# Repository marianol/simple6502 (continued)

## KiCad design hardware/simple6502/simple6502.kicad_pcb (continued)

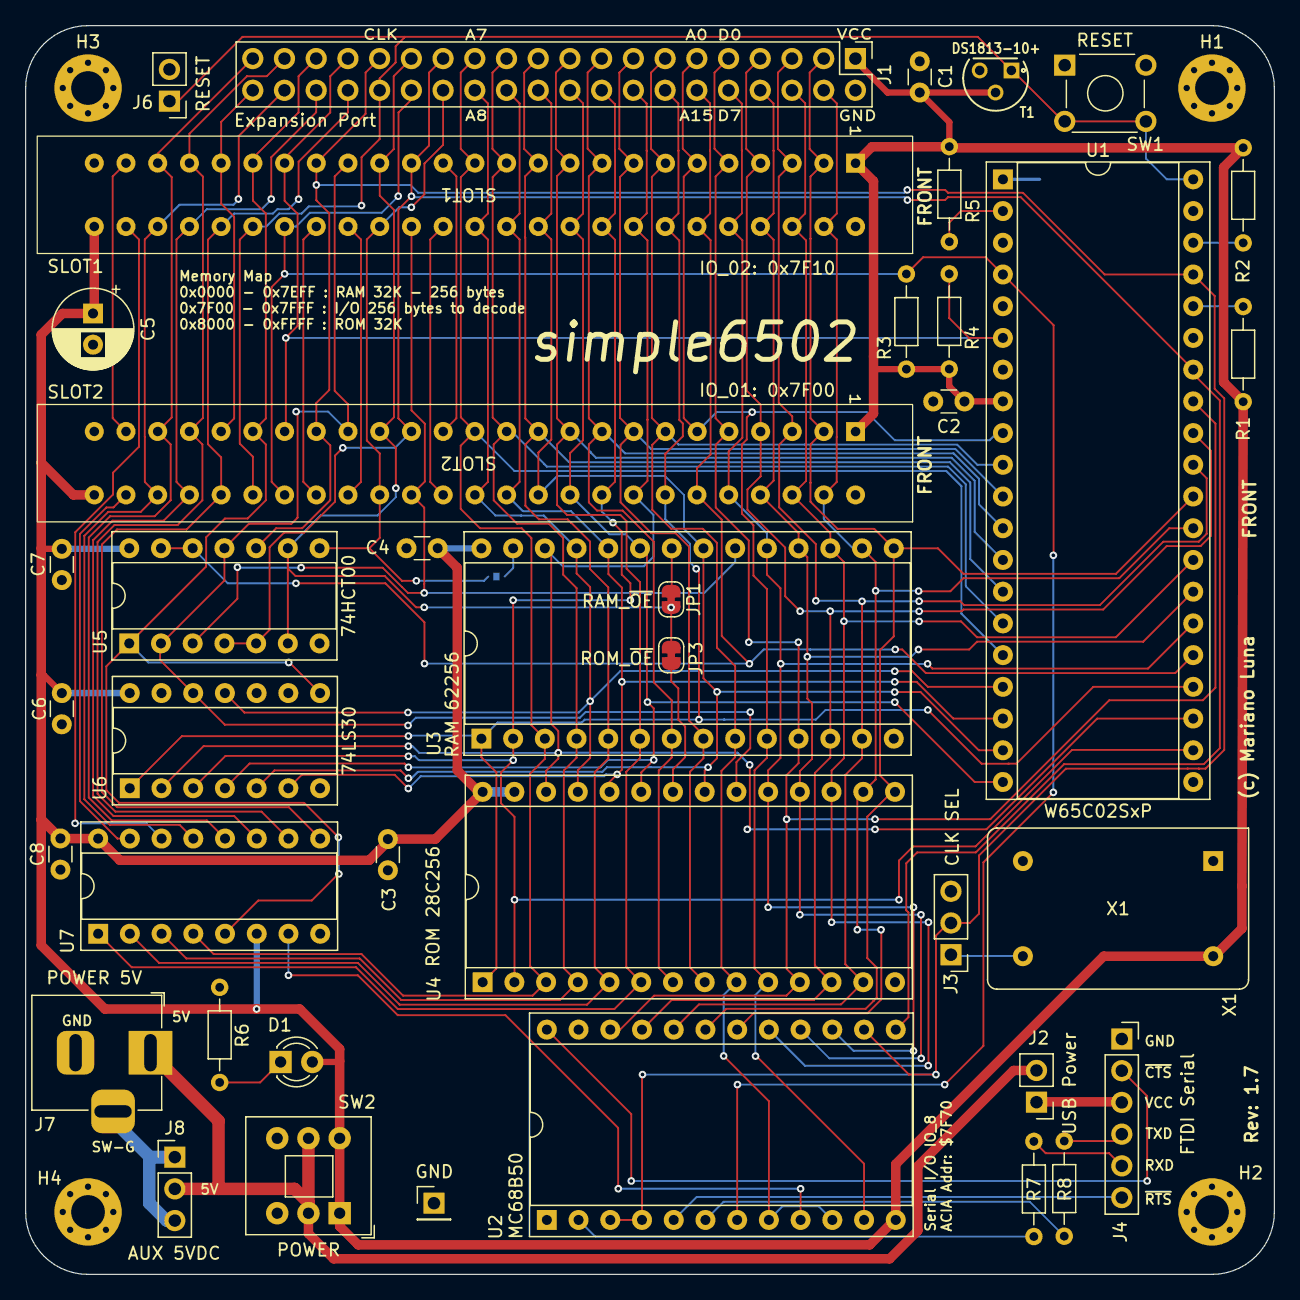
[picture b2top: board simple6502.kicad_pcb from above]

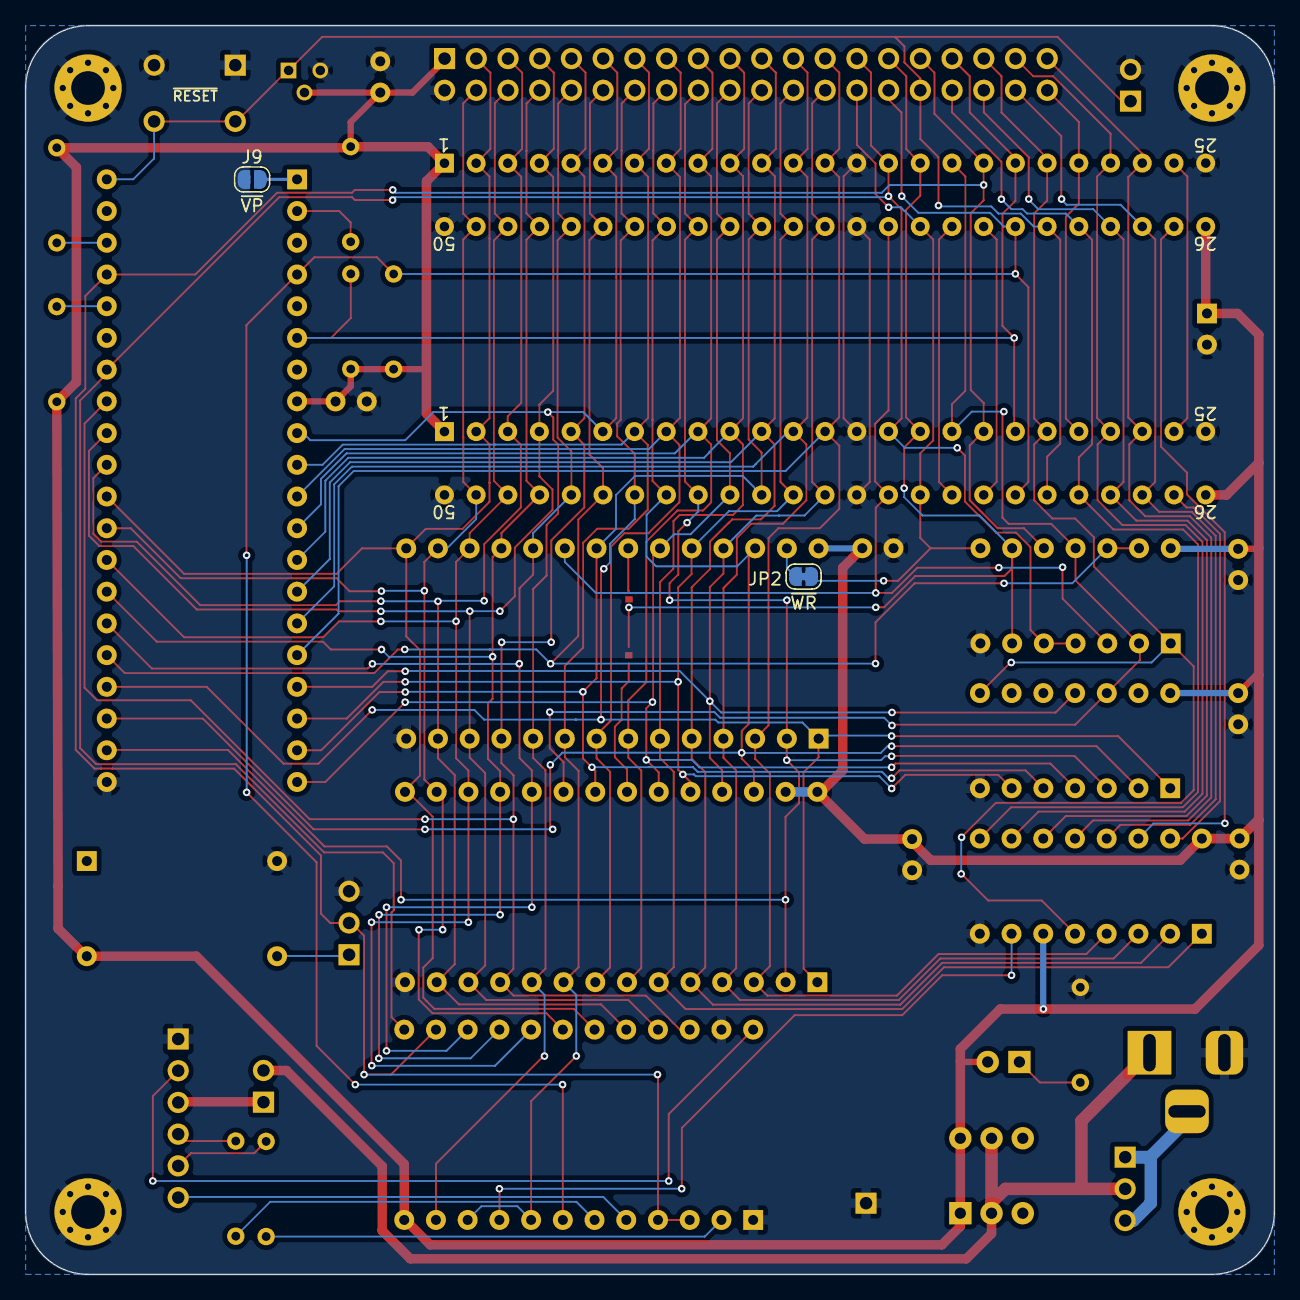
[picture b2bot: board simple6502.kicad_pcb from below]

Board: 2 copper layers, 100.0 x 100.0 mm, 46 parts (2 on the bottom side), 66 nets.

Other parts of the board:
SLOT1: IO_02: 0x7F10; EDAC 395-050-520-201

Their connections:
A0: SLOT1.6; also elsewhere on the board
A1: SLOT1.7; also elsewhere on the board
A2: SLOT1.8; also elsewhere on the board
A3: SLOT1.9; also elsewhere on the board
A4: SLOT1.10; also elsewhere on the board
A5: SLOT1.11; also elsewhere on the board
A6: SLOT1.12; also elsewhere on the board
A7: SLOT1.13; also elsewhere on the board
A8: SLOT1.38; also elsewhere on the board
A9: SLOT1.39; also elsewhere on the board
A10: SLOT1.40; also elsewhere on the board
A11: SLOT1.41; also elsewhere on the board
A12: SLOT1.42; also elsewhere on the board
A13: SLOT1.43; also elsewhere on the board
A14: SLOT1.44; also elsewhere on the board
A15: SLOT1.45; also elsewhere on the board
BUS_21: SLOT1.21; also elsewhere on the board
BUS_24: SLOT1.24; also elsewhere on the board
BUS_33: SLOT1.33; also elsewhere on the board
BUS_34: SLOT1.34; also elsewhere on the board
CLK: SLOT1.18; also elsewhere on the board
D0: SLOT1.5; also elsewhere on the board
D1: SLOT1.4; also elsewhere on the board
D2: SLOT1.3; also elsewhere on the board
D3: SLOT1.2; also elsewhere on the board
D4: SLOT1.49; also elsewhere on the board
D5: SLOT1.48; also elsewhere on the board
D6: SLOT1.47; also elsewhere on the board
D7: SLOT1.46; also elsewhere on the board
GND: SLOT1.14, SLOT1.25, SLOT1.37, SLOT1.50; also elsewhere on the board
R~W: SLOT1.15; also elsewhere on the board
VCC: SLOT1.1, SLOT1.26; also elsewhere on the board
~IO_02: SLOT1.27; also elsewhere on the board
~IO_03: SLOT1.28; also elsewhere on the board
~IO_04: SLOT1.23; also elsewhere on the board
~IO_05: SLOT1.29; also elsewhere on the board
~IO_06: SLOT1.22; also elsewhere on the board
~IO_07: SLOT1.30; also elsewhere on the board
~IO_CS: SLOT1.20; also elsewhere on the board
~IRQ: SLOT1.32; also elsewhere on the board
~NMI: SLOT1.19; also elsewhere on the board
~RAM_CS: SLOT1.36; also elsewhere on the board
~RD: SLOT1.16; also elsewhere on the board
~RESET: SLOT1.31; also elsewhere on the board
~ROM_CS: SLOT1.17; also elsewhere on the board
~WR: SLOT1.35; also elsewhere on the board

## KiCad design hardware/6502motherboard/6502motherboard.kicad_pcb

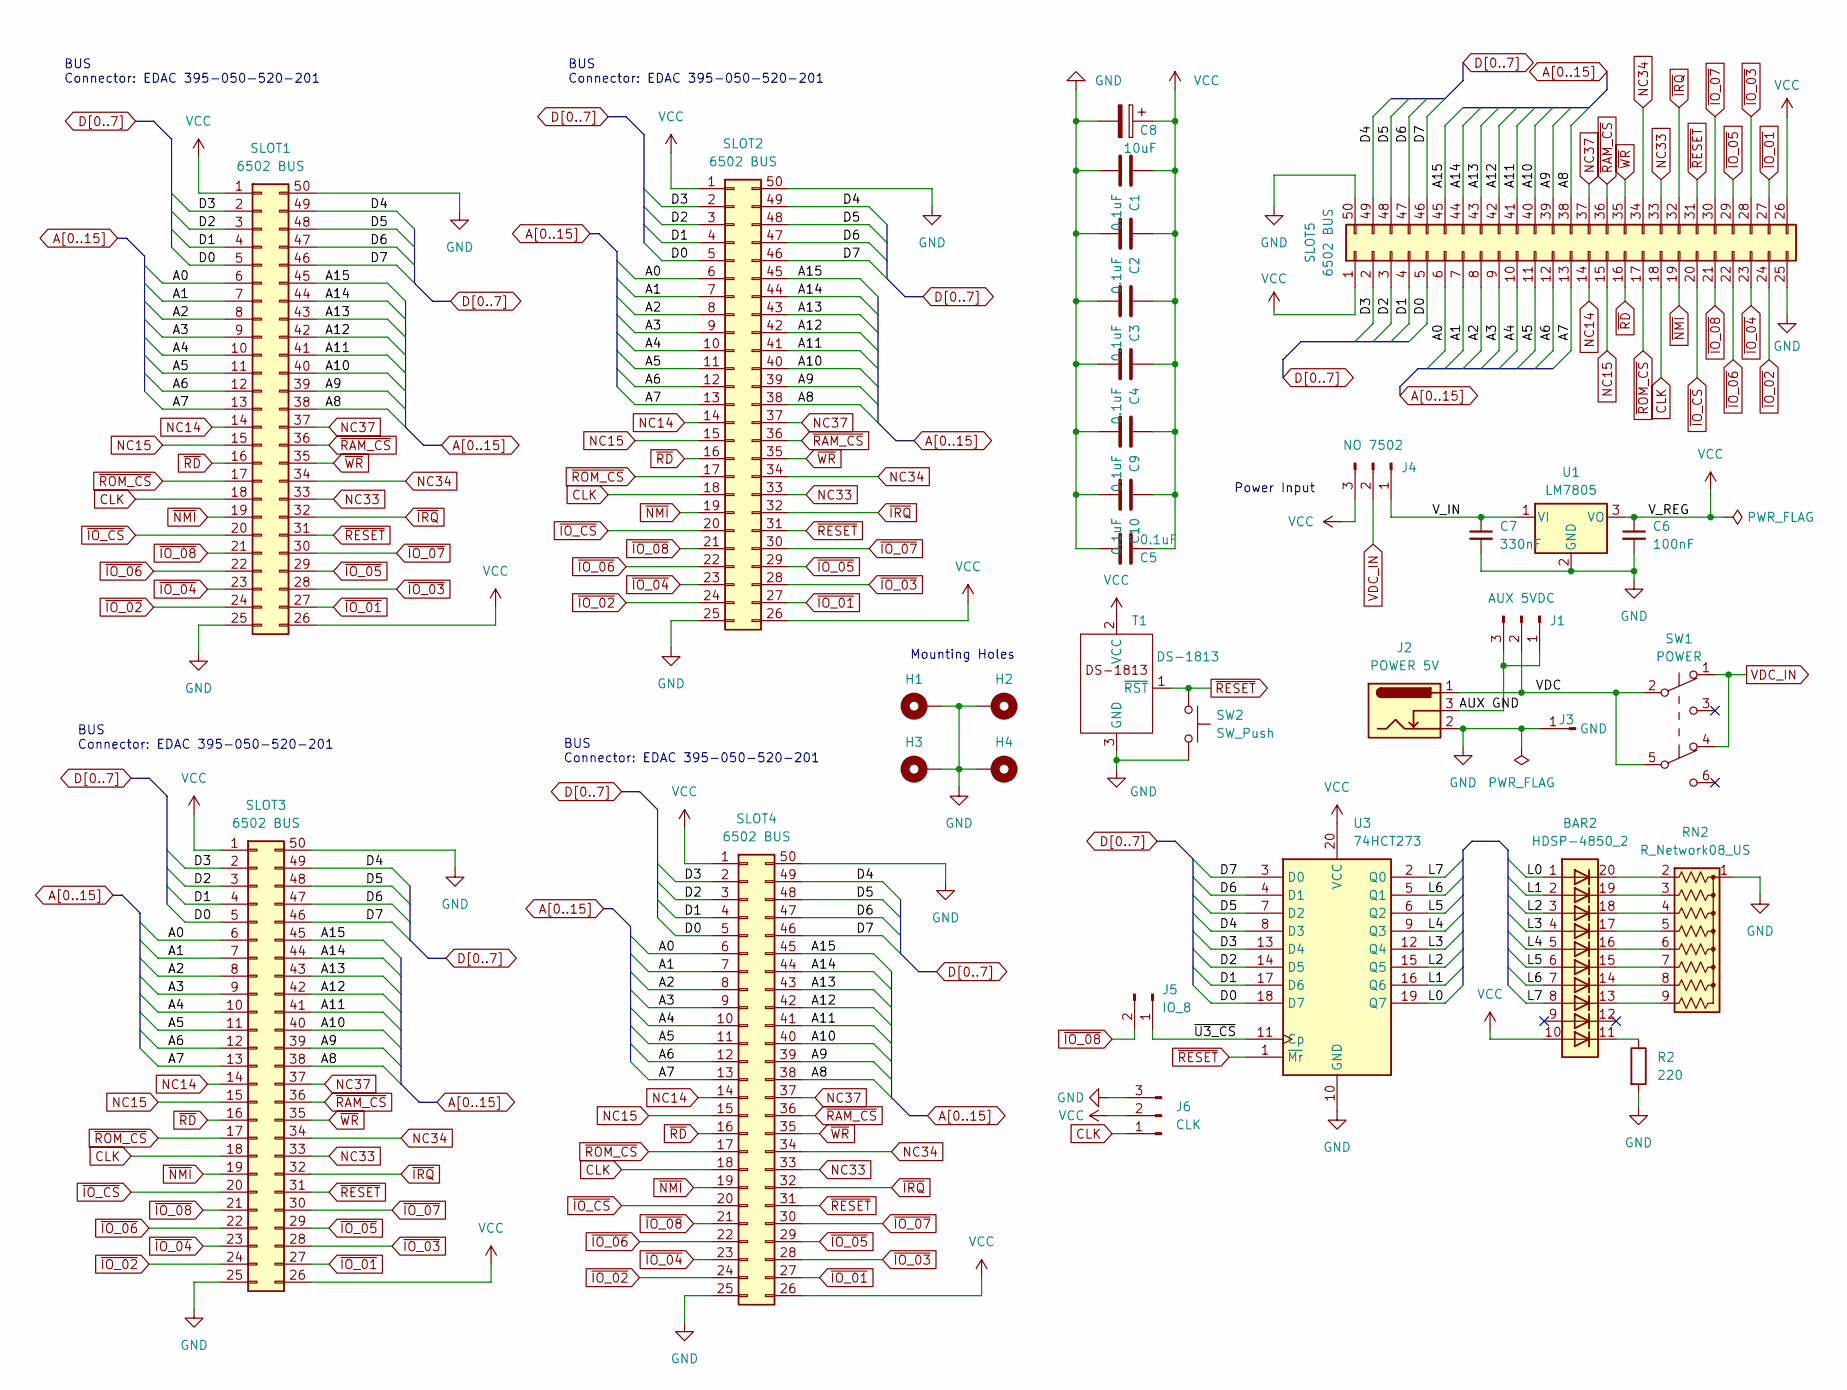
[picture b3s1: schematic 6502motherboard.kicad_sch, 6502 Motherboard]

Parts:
BAR2: HDSP-4850_2; HDSP-4850
C1, C2, C3, C4, C5, C9, C10: 0.1uF; C_Disc_D3.0mm_W1.6mm_P2.50mm
C6: 100nF; C_Disc_D3.0mm_W1.6mm_P2.50mm
C7: 330nF; C_Disc_D3.0mm_W1.6mm_P2.50mm
C8: 10uF; CP_Radial_D6.3mm_P2.50mm
H1, H2, H3, H4: M; MountingHole_2.7mm_M2.5_Pad_Via
J1: AUX 5VDC; PinHeader_1x03_P2.54mm_Vertical
J2: POWER 5V; BarrelJack_Horizontal
J3: GND; PinHeader_1x01_P2.54mm_Vertical
J4: NO 7502; PinHeader_1x03_P2.54mm_Vertical
J5: IO_8; PinHeader_1x02_P2.54mm_Vertical
J6: CLK; JST_PH_B3B-PH-K_1x03_P2.00mm_Vertical
R2: 220; R_Axial_DIN0204_L3.6mm_D1.6mm_P7.62mm_Horizontal
RN2: R_Network08_US; R_Array_SIP9
SLOT1, SLOT2, SLOT3, SLOT4: 6502 BUS; EDAC 395-050-520-201
SLOT5: 6502 BUS; PinHeader_2x25_P2.54mm_Vertical_Counter_Clockwise
SW1: POWER; SW_Push_2P2T_Toggle_CK_PVA2OAH5xxxxxxV2
SW2: SW_Push; SW_PUSH_6mm_H5mm
T1: DS-1813; 21-0248A_MAXIM
U1: LM7805; TO-220-3_Horizontal_TabDown
U3: 74HCT273; DIP-20_W7.62mm_Socket

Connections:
/AUX GND: J1.1, J1.3, J2.3
/L0: BAR2.1 (A), U3.19 (Q7)
/L1: BAR2.2 (A), U3.16 (Q6)
/L2: BAR2.3 (A), U3.15 (Q5)
/L3: BAR2.4 (A), U3.12 (Q4)
/L4: BAR2.5 (A), U3.9 (Q3)
/L5: BAR2.6 (A), U3.6 (Q2)
/L6: BAR2.7 (A), U3.5 (Q1)
/L7: BAR2.8 (A), U3.2 (Q0)
/VDC: J1.2, J2.1, SW1.2 (B), SW1.5 (B)
/V_IN: C7.1, J4.1, U1.1 (VI)
/~U3_CS: J5.1, U3.11 (Cp)
A0: SLOT1.6, SLOT2.6, SLOT3.6, SLOT4.6, SLOT5.6
A1: SLOT1.7, SLOT2.7, SLOT3.7, SLOT4.7, SLOT5.7
A2: SLOT1.8, SLOT2.8, SLOT3.8, SLOT4.8, SLOT5.8
A3: SLOT1.9, SLOT2.9, SLOT3.9, SLOT4.9, SLOT5.9
A4: SLOT1.10, SLOT2.10, SLOT3.10, SLOT4.10, SLOT5.10
A5: SLOT1.11, SLOT2.11, SLOT3.11, SLOT4.11, SLOT5.11
A6: SLOT1.12, SLOT2.12, SLOT3.12, SLOT4.12, SLOT5.12
A7: SLOT1.13, SLOT2.13, SLOT3.13, SLOT4.13, SLOT5.13
A8: SLOT1.38, SLOT2.38, SLOT3.38, SLOT4.38, SLOT5.38
A9: SLOT1.39, SLOT2.39, SLOT3.39, SLOT4.39, SLOT5.39
A10: SLOT1.40, SLOT2.40, SLOT3.40, SLOT4.40, SLOT5.40
A11: SLOT1.41, SLOT2.41, SLOT3.41, SLOT4.41, SLOT5.41
A12: SLOT1.42, SLOT2.42, SLOT3.42, SLOT4.42, SLOT5.42
A13: SLOT1.43, SLOT2.43, SLOT3.43, SLOT4.43, SLOT5.43
A14: SLOT1.44, SLOT2.44, SLOT3.44, SLOT4.44, SLOT5.44
A15: SLOT1.45, SLOT2.45, SLOT3.45, SLOT4.45, SLOT5.45
CLK: J6.1, SLOT1.18, SLOT2.18, SLOT3.18, SLOT4.18, SLOT5.18
D0: SLOT1.5, SLOT2.5, SLOT3.5, SLOT4.5, SLOT5.5, U3.18 (D7)
D1: SLOT1.4, SLOT2.4, SLOT3.4, SLOT4.4, SLOT5.4, U3.17 (D6)
D2: SLOT1.3, SLOT2.3, SLOT3.3, SLOT4.3, SLOT5.3, U3.14 (D5)
D3: SLOT1.2, SLOT2.2, SLOT3.2, SLOT4.2, SLOT5.2, U3.13 (D4)
D4: SLOT1.49, SLOT2.49, SLOT3.49, SLOT4.49, SLOT5.49, U3.8 (D3)
D5: SLOT1.48, SLOT2.48, SLOT3.48, SLOT4.48, SLOT5.48, U3.7 (D2)
D6: SLOT1.47, SLOT2.47, SLOT3.47, SLOT4.47, SLOT5.47, U3.4 (D1)
D7: SLOT1.46, SLOT2.46, SLOT3.46, SLOT4.46, SLOT5.46, U3.3 (D0)
GND: C1.2, C2.2, C3.2, C4.2, C5.2, C6.2, C7.2, C8.2, C9.2, C10.2, H1.1, H2.1, H3.1, H4.1, J2.2, J3.1, J6.3, R2.2, RN2.1 (common), SLOT1.25, SLOT1.50, SLOT2.25, SLOT2.50, SLOT3.25, SLOT3.50, SLOT4.25, SLOT4.50, SLOT5.25, SLOT5.50, SW2.2, T1.3 (GND), U1.2 (GND), U3.10 (GND)
NC14: SLOT1.14, SLOT2.14, SLOT3.14, SLOT4.14, SLOT5.14
NC15: SLOT1.15, SLOT2.15, SLOT3.15, SLOT4.15, SLOT5.15
NC33: SLOT1.33, SLOT2.33, SLOT3.33, SLOT4.33, SLOT5.33
NC34: SLOT1.34, SLOT2.34, SLOT3.34, SLOT4.34, SLOT5.34
NC37: SLOT1.37, SLOT2.37, SLOT3.37, SLOT4.37, SLOT5.37
unnamed: BAR2.11 (K), R2.1
unnamed: BAR2.20 (K), RN2.2 (R1)
unnamed: BAR2.19 (K), RN2.3 (R2)
unnamed: BAR2.18 (K), RN2.4 (R3)
unnamed: BAR2.17 (K), RN2.5 (R4)
unnamed: BAR2.16 (K), RN2.6 (R5)
unnamed: BAR2.15 (K), RN2.7 (R6)
unnamed: BAR2.14 (K), RN2.8 (R7)
unnamed: BAR2.13 (K), RN2.9 (R8)
VCC: BAR2.10 (A), C1.1, C2.1, C3.1, C4.1, C5.1, C6.1, C8.1, C9.1, C10.1, J4.3, J6.2, SLOT1.1, SLOT1.26, SLOT2.1, SLOT2.26, SLOT3.1, SLOT3.26, SLOT4.1, SLOT4.26, SLOT5.1, SLOT5.26, T1.2 (VCC), U1.3 (VO), U3.20 (VCC)
VDC_IN: J4.2, SW1.1 (A), SW1.4 (A)
~IO_01: SLOT1.27, SLOT2.27, SLOT3.27, SLOT4.27, SLOT5.27
~IO_02: SLOT1.24, SLOT2.24, SLOT3.24, SLOT4.24, SLOT5.24
~IO_03: SLOT1.28, SLOT2.28, SLOT3.28, SLOT4.28, SLOT5.28
~IO_04: SLOT1.23, SLOT2.23, SLOT3.23, SLOT4.23, SLOT5.23
~IO_05: SLOT1.29, SLOT2.29, SLOT3.29, SLOT4.29, SLOT5.29
~IO_06: SLOT1.22, SLOT2.22, SLOT3.22, SLOT4.22, SLOT5.22
~IO_07: SLOT1.30, SLOT2.30, SLOT3.30, SLOT4.30, SLOT5.30
~IO_08: J5.2, SLOT1.21, SLOT2.21, SLOT3.21, SLOT4.21, SLOT5.21
~IO_CS: SLOT1.20, SLOT2.20, SLOT3.20, SLOT4.20, SLOT5.20
~IRQ: SLOT1.32, SLOT2.32, SLOT3.32, SLOT4.32, SLOT5.32
~NMI: SLOT1.19, SLOT2.19, SLOT3.19, SLOT4.19, SLOT5.19
~RAM_CS: SLOT1.36, SLOT2.36, SLOT3.36, SLOT4.36, SLOT5.36
~RD: SLOT1.16, SLOT2.16, SLOT3.16, SLOT4.16, SLOT5.16
~RESET: SLOT1.31, SLOT2.31, SLOT3.31, SLOT4.31, SLOT5.31, SW2.1, T1.1 (~RST), U3.1 (~Mr)
~ROM_CS: SLOT1.17, SLOT2.17, SLOT3.17, SLOT4.17, SLOT5.17
~WR: SLOT1.35, SLOT2.35, SLOT3.35, SLOT4.35, SLOT5.35

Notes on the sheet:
Mounting Holes
Power Input
BUS Connector: EDAC 395-050-520-201

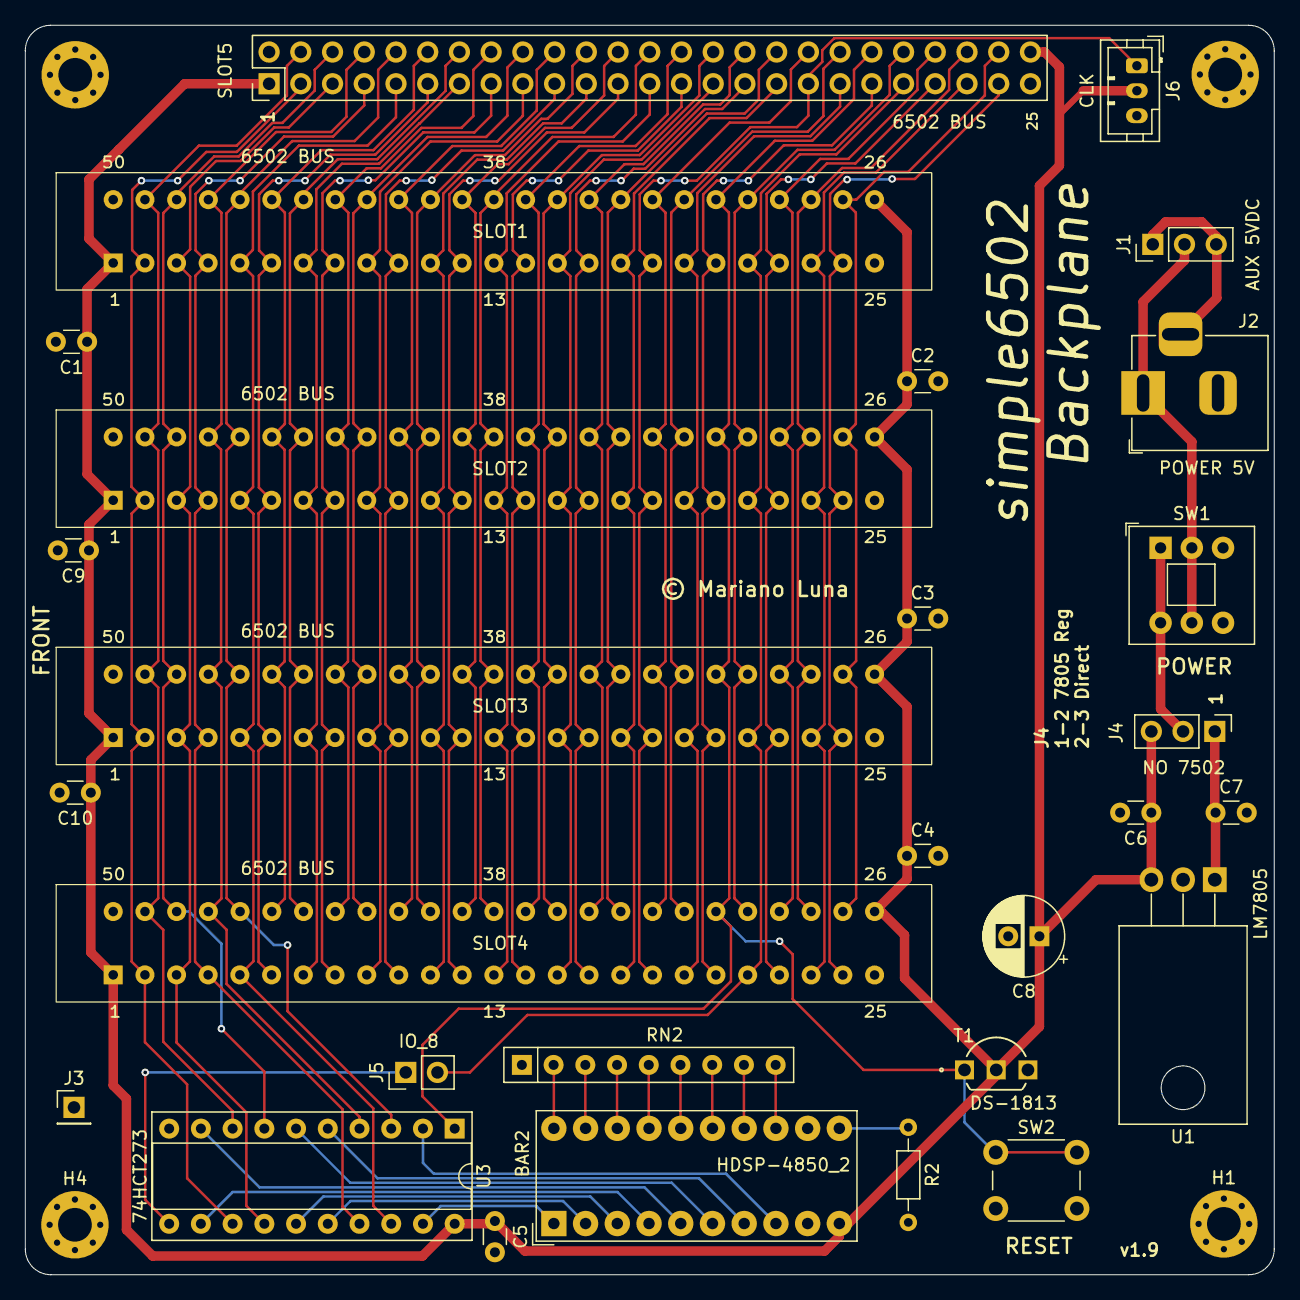
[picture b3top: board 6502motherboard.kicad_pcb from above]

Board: 2 copper layers, 100.0 x 100.0 mm, 33 parts (0 on the bottom side), 70 nets.

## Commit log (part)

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2023-09-21 adding .gitignore for KiCad
2023-09-21 Kicad project added + standard structure
2023-09-22 Starter project and libraries.
2023-09-22 Kicad 7 update, 6502 libraries, moved datasheets to their own folder
2023-09-22 New .gitignore to match KiCad 7
2023-09-22 Cleanup
2023-09-22 Wired CPU, RAM and ROM
2023-09-22 Reset, Clock, Expansion and Power
2023-09-22 Fixed Bus label names
2023-09-22 Memory decoder v1
2023-09-22 Main board schematic complete v0.0.1
2023-09-22 Footprint round 1
2023-09-23 Added Apple II connector footprint and 3d model
2023-09-23 v0.5 Schematic complete and footprint assigned.
2023-09-23 Updated to ignore .lck files
2023-09-23 PCB defaults set and components dropped
2023-09-23 First PCB Layout
2023-09-23 Fixed Apple Connector 3D model, routing started
2023-09-24 Routing PCB
2023-09-24 More PCB Routing
2023-09-24 Much More PCB Routing - Clean DRC
2023-09-24 Mostly done, Address and Data finished
2023-09-25 rearange the bus for better routing
2023-09-25 PCB fully routed clean DRC
2023-09-25 added IO 3-8 decoder
2023-09-26 more pin rearrangment in bus connector
2023-09-26 Routing v1 finished - DRC passed
2023-09-26 Schematics updated to v1 - ERC passed
2023-09-26 PCB images v1
2023-10-01 Relocated reset
2023-10-02 adding Debug leds in IO_8
2023-10-02 version 1.1
2023-10-02 ReadMe update
2023-10-02 fix readme
2023-10-14 flush changes
2023-10-15 clean pcb board style
2023-10-16 cpu board only ready
2023-10-16 cpu board 1.0 PCB ready
2023-10-17 cpu board 1.0 PCB minor routing tidy up
2023-10-17 adding schematic pdf and board images
2023-10-17 CPU Board v1.2 complete
2023-10-17 Protoboard v0.5
2023-10-17 Protoboard v1.0
2023-10-17 All in One PCB v1.1
2023-10-17 motherboard v0.1
2023-10-17 Fixed 6502 Pinout, routed bus and power
2023-10-18 v1.0 Motherboard Ready
2023-10-26 v1.6 Motherboard Complete
2023-10-26 v1.5 CPU Board Complete
2023-11-04 Motherboard added 7805 regulator
2023-11-04 Schematic and PCB cleanup
2023-11-04 I_O8 Jumper and more PCB cleanup
2023-11-14 rev 1.8 new pcb optimized power routing
2023-11-24 rev 1.8.1 pcb routed external connector in top layer
2023-11-24 rev 1.9 complete
2023-11-24 Schematic rev 1.6 complete
2024-03-07 cleanup and minor changes
2024-03-09 new all in one design with ACIA 68B50
2024-03-10 Corrected 6502 Bus pinout - re-routed
2024-03-27 PCB ready DRC passed
2024-03-27 Updated VCC routing
2024-06-15 add the 40 pin header
2024-06-26 port wired, new slot pinout
2024-06-27 minor route changes
2024-06-27 renumer components based on PCB placement
2024-06-27 minor silkscreen and trace tidy up
2024-06-27 new PCB pics
2024-06-27 minor slikscreen additions
2024-06-27 updated ReadME and memory map in the schematic
2024-06-27 typo fix for {\textunderscore}
2024-06-27 added license to the read me
2024-06-27 Squashed commit of the following:
    commit 7c3efda86e123a872d37b7a0967bfebff1f0e87c
    Author: Mariano Luna <marianolu@gmail.com>
    Date: Wed Jun 26 21:29:25 2024 -0500
    added license to the read me
    commit 04e24ff3751ecfd7aa1644195e6f678569023e69
    Author: Mariano Luna <marianolu@gmail.com>
2024-06-27 Rev 1.5 complete
2024-06-27 fixed pinout + power led
2024-06-27 Protoboard Rev 1.2
    Fixed pinout of connector and added power led
2024-07-03 Version 1.6 Final
    Added solder pads just in case
2024-07-03 ProtoCard Rev 1.2
2024-07-03 ProtoCard Rev:1.2 Gerbers
2024-07-03 simple6502 Rev:1.6 Final
2024-07-03 simple6502 Rev:1.6 Gerbers
2024-07-03 Board Images rev 1.6
2024-07-03 Update README.md
    Added board pic
2024-07-17 Revision 1.6.1 Moved C5 and added C8
    Moved C5 to make space for a slim ZIF for the ROM.
2024-07-17 Rev. 1.6.1 Silkscreen and labels
    Added labels fro the FTDI, moved some other that got covered by sockets.
2024-07-17 Added Gallery with bare PCBs
    PCBs done in PCB Way revision 1.6
2024-07-17 Update README.md
    Added link to PCB picture
2024-07-20 firmware dev environment and config
2024-07-20 ACIA datasheet for reference
2024-07-20 Defines file and simple board test rom
2024-07-21 make script complete
2024-07-21 test rom build v0.1
2024-07-22 PCB Rev 1.7 - rewire FTDI
    using a more standard pinout for the FTDI header
2024-07-22 ACIA register correction
2024-07-22 simple board test loop NOP
2024-07-22 rev 1.6 First BIOS Test all OK
    Board test OK, Serial working
2024-07-23 adding WozMon to the BIOS
2024-07-23 Update ReadMe with Rev.1.6 tests
2024-07-23 readme for the firmware folder
2024-07-23 BIOS v 0.1.0 boots to Wozmon
    Tested and working
2024-07-23 IO Card Initial commit
    VIA 6522 IO card and other goodies
2024-07-23 flipped card PCB to face the correct way
2024-07-23 Rev: 0.5 basic VIA wiring
2024-07-23 Rev 0.6 2 VIAs ready to route
2024-07-25 syntax cleanup
2024-07-25 wozmon mods to handle lower case
2024-07-26 wozmon comments and cleanup
2024-07-26 wozmon: now progras can RTI back to the monitor
    wozmon
2024-07-26 BIOS v 0.1.2: minor updates in bios and wozmon, cleanup defines
2024-07-26 BIOS v0.1.3: minor tweaks so Wozmon fits in 256 bytes
2024-07-28 added all VIA Regs and minor comments
2024-07-29 simple test for VIA
2024-07-29 new USR program config to assemble for running in memory
2024-07-29 USR make scrip output can be copy pasted into WozMon
2024-07-30 Added SPI comms protocol doc
2024-07-30 stub for SD card initi
2024-07-30 fix typo
2024-07-30 SPI initialization docs
2024-07-30 wozmon now displays 16 locations per line
2024-07-31 minor doc updates adn _CS constant
2024-08-01 more cleanup and comments
2024-08-01 IO Card is Rev 1.0 PCB complete
2024-08-01 Updates some labels
2024-08-07 IOCard with SMD bypass caps
2024-08-07 more comments
2024-08-07 SPI display datasheet
2024-08-07 SPI routines for Port A VIA 1
2024-08-08 Adding more info on R7 responses
2024-08-08 a v0.5 of the SD card init not tested
2024-08-08 SD SPI v0.6
2024-08-14 Added ZP variables for Mon processor status
2024-08-14 adding print CPU status routine
2024-08-17 SPI 0.6.1
2024-08-17 IO Card rev 1.1 + smd caps
2026-04-23 working files to sync
